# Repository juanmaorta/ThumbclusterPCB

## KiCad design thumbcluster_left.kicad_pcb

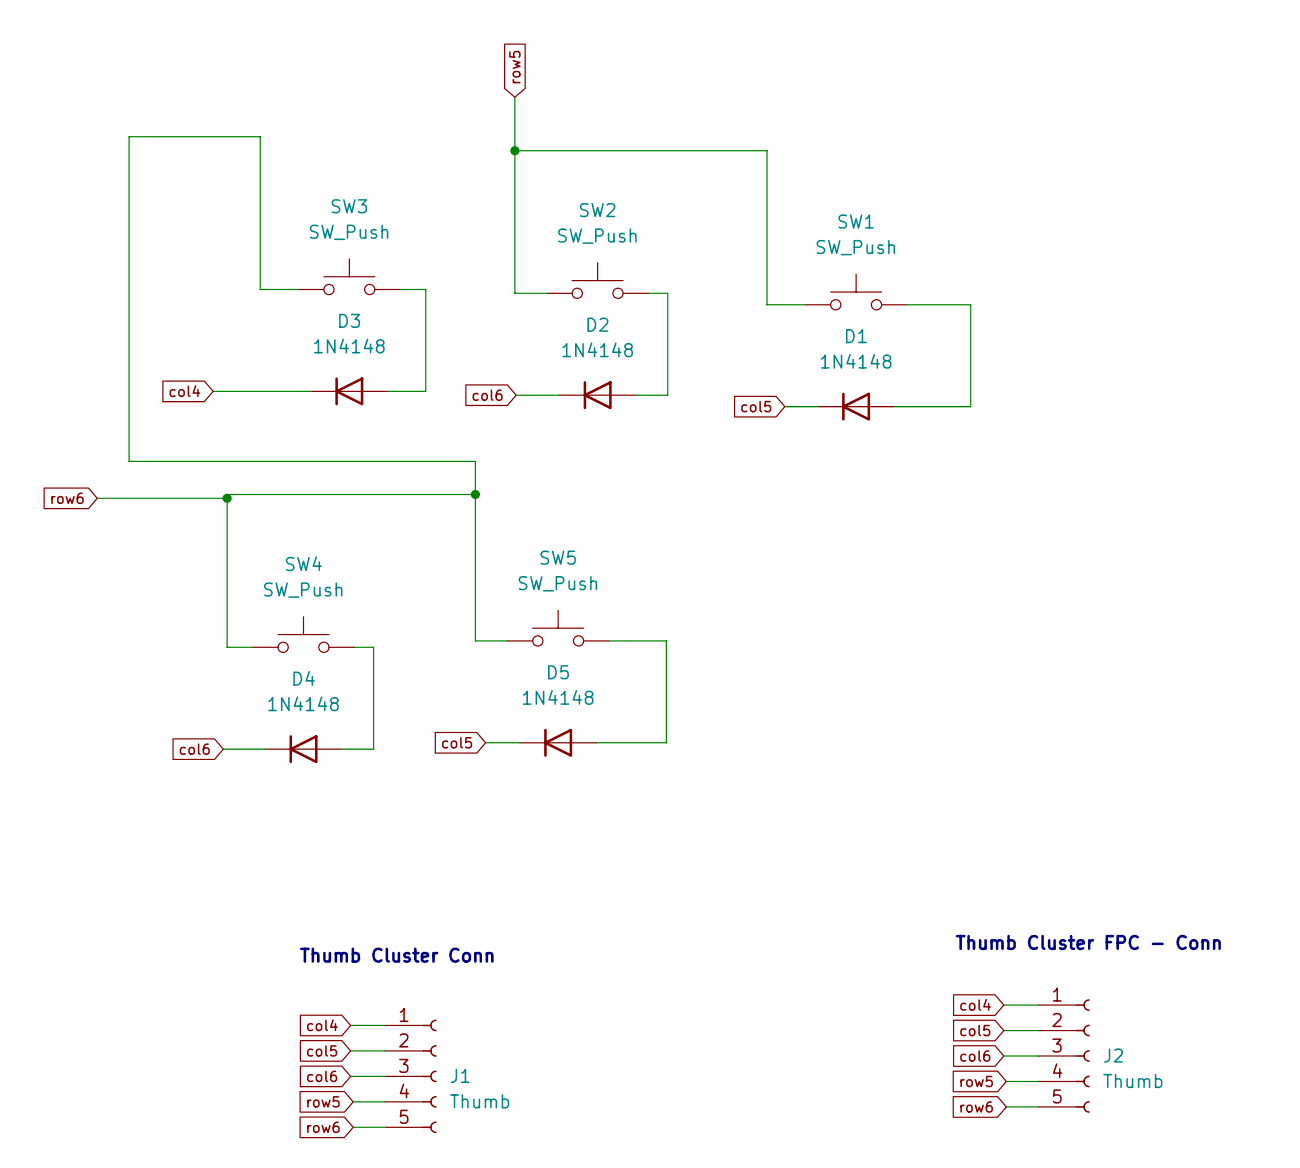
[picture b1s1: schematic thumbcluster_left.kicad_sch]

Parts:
D1, D2, D3, D4, D5: 1N4148; THT-SOD123 - Diode
J1: Thumb; PinSocket_1x05_P2.00mm_Vertical
J2: Thumb; Molex_200528-0050_1x05-1MP_P1.00mm_Horizontal
SW1, SW2, SW3, SW4, SW5: SW_Push; SW_MX

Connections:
unnamed: D1.2 (A), SW1.2
unnamed: D2.2 (A), SW2.2
unnamed: D3.2 (A), SW3.2
unnamed: D4.2 (A), SW4.2
unnamed: D5.2 (A), SW5.2
col4: D3.1 (K), J1.1, J2.1
col5: D1.1 (K), D5.1 (K), J1.2, J2.2
col6: D2.1 (K), D4.1 (K), J1.3, J2.3
row5: J1.4, J2.4, SW1.1, SW2.1
row6: J1.5, J2.5, SW3.1, SW4.1, SW5.1

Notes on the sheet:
Thumb Cluster Conn
Thumb Cluster FPC - Conn

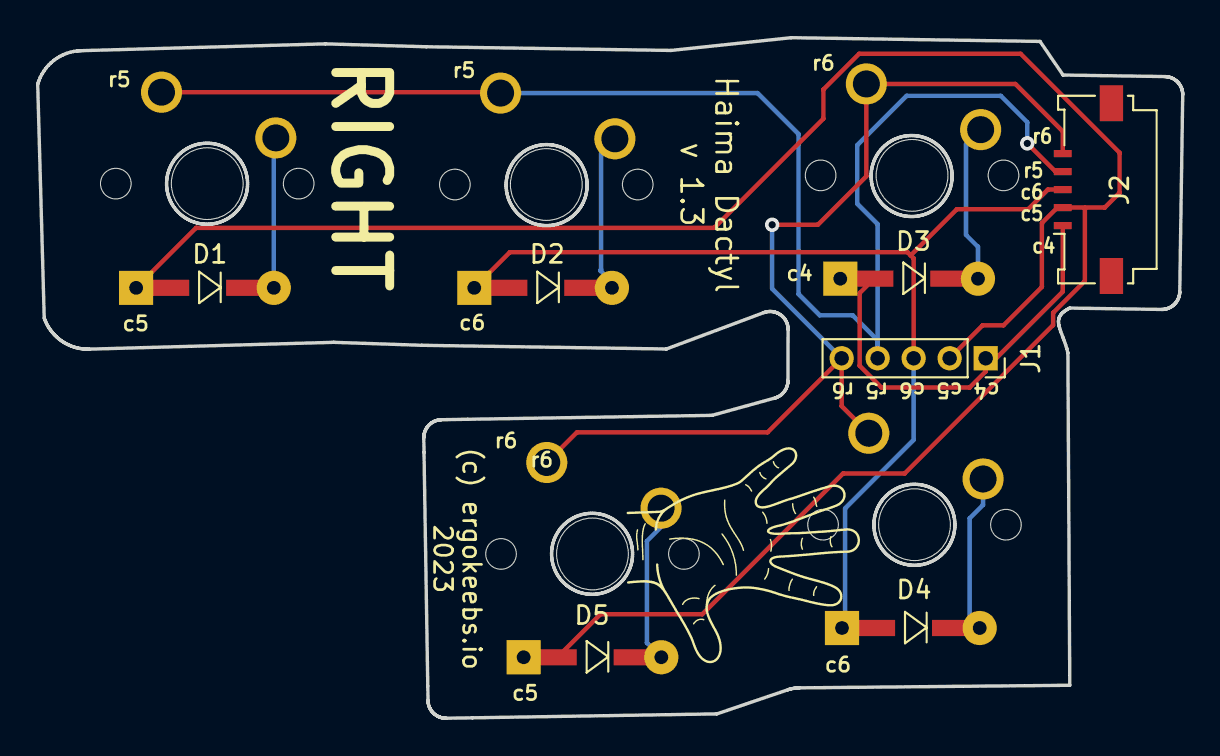
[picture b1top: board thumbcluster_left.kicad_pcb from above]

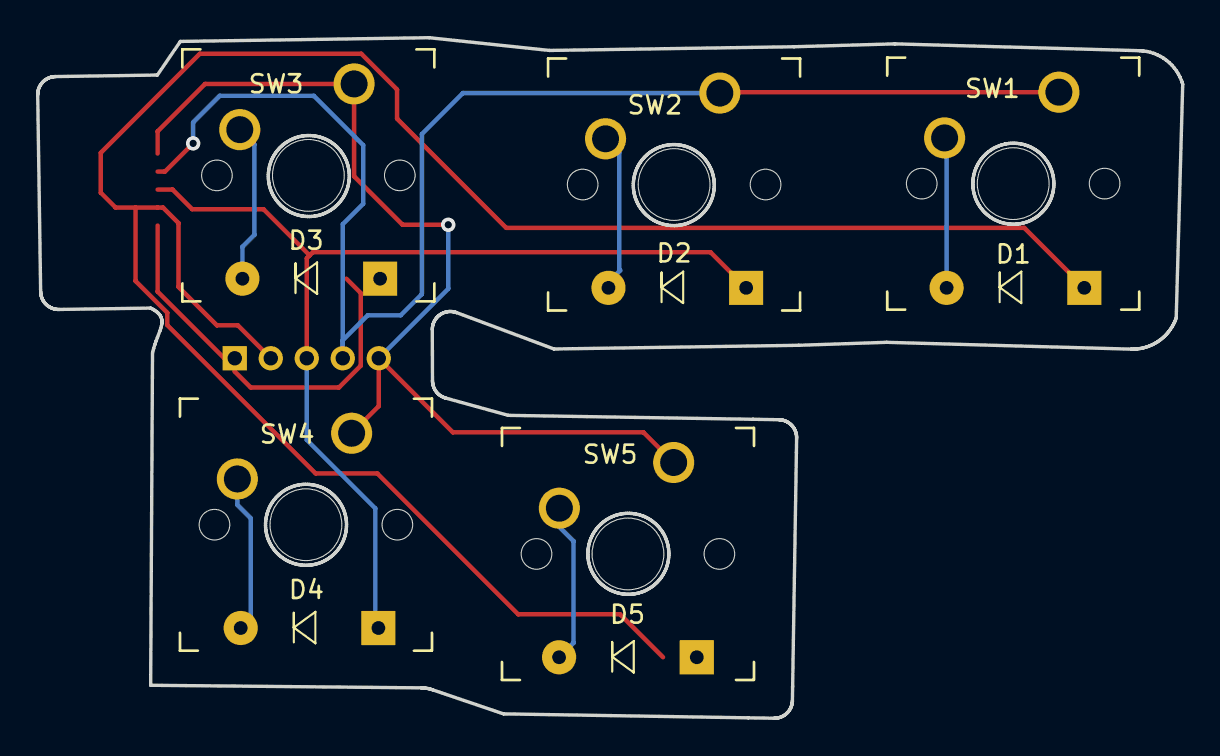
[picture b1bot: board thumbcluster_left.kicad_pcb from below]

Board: 2 copper layers, 63.6 x 37.8 mm, 12 parts (10 on the bottom side), 10 nets.

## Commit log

2023-02-09 Left thumbcluster - hotswap switches
2023-02-09 Through hole switches
2023-03-09 Update diode footprint
2023-03-15 Complete net refactor
2023-05-31 Routing
2023-06-06 Silkscreening
